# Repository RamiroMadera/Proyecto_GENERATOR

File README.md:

# GENERATOR 🎲  
**Consola electrónica portátil para jugar a la Generala**  
Dispositivo desarrollado con la **EDU-CIAA-NXP** que emula tiradas de dados, combinaciones y puntajes del tradicional juego de Generala. Integra una pantalla táctil, efectos de sonido, sensores de movimiento y una interfaz gráfica atractiva, todo en un sistema autónomo alimentado por batería.

---

## 🎮 Características principales

- **Simulación de tiradas de Generala**
  - Aleatorización de dados entre 1 y 6.
  - Selección de dados para conservar y volver a tirar.
  - Evaluación automática del puntaje y combinaciones.

- **Pantalla gráfica interactiva**
  - Display TFT 2.8" con controlador **ILI9341**.
  - Interfaz táctil basada en **XPT2046** para seleccionar dados y comenzar partidas.

- **Detección de movimiento**
  - Sensor **MPU6050** para identificar la agitación del dispositivo y gatillar la tirada.

- **Sistema de audio**
  - Generación de sonidos con DAC de 10 bits.
  - Amplificación mediante **LM386**.
  - Efectos que acompañan la agitación, la tirada y la obtención de una Generala.

- **Portabilidad total**
  - Alimentado por una batería externa de **5100 mAh**, con una autonomía estimada de más de **16 horas** de juego continuo.

---

## 🧠 Arquitectura del sistema

- **Microcontrolador:** EDU-CIAA-NXP  
- **Interacción por estados:** Inicio → Reposo → Sacudiendo 
- **Firmware en C** desarrollado bajo **CIAA Launcher** 

---

## 📦 Instalación

1. Clona el repositorio:
   ```bash
   git clone https://github.com/RamiroMadera/Proyecto_GENERATOR.git
   ```
2. Abrí el proyecto con CIAA Launcher.
3. Compila y carga el firmware a la placa.
4. Conecta los periféricos según el [esquemático incluido](https://github.com/RamiroMadera/Proyecto_GENERATOR/blob/main/kicad/GENERATOR_Esquematico.pdf).
5. ¡Listo para jugar!

---

## 📚 Documentación técnica

El proyecto cuenta con documentación completa en el informe final del curso "Taller de Proyecto I" de la Facultad de Ingeniería (UNLP), que incluye:

- Requerimientos de hardware y software
- Diseño esquemático y PCB en KiCad
- Arquitectura del firmware y máquina de estados
- Métodos de aleatorización
- Validación del sistema y videos de prueba

[📄 Informe Final (PDF)](https://github.com/RamiroMadera/Proyecto_GENERATOR/blob/main/docs/InformeFinal-Grupo8-TallerDeProyectoI.pdf)

---

## 🧪 Validación y videos

Se ha validado el correcto funcionamiento de todos los requerimientos. Puedes ver los resultados en esta [playlist de YouTube](https://www.youtube.com/playlist?list=PLVBSSKjP-CQ1Y1-SsgbkpVqvSBivJ-5Vr), que muestra:

- Encendido/apagado  
- Tiradas completas  
- Selección de dados  
- Sonido y efectos especiales  
- Reconocimiento de combinaciones y puntajes

---

## 🛠️ Créditos

**Autores:**  
- Tobias Garcia Iacovelli  
- Ramiro Madera  
- Ulises Pereira  

Este proyecto fue desarrollado como parte del curso **Taller de Proyecto I** en la **Facultad de Ingeniería, Universidad Nacional de La Plata**.

---

## 🚀 Próximos pasos

- Añadir sistema de historial de puntajes  
- Incorporar carcasa protectora  
- Expansión a múltiples juegos de dados  
- Conectividad en red para multijugador o leaderboard en la nube

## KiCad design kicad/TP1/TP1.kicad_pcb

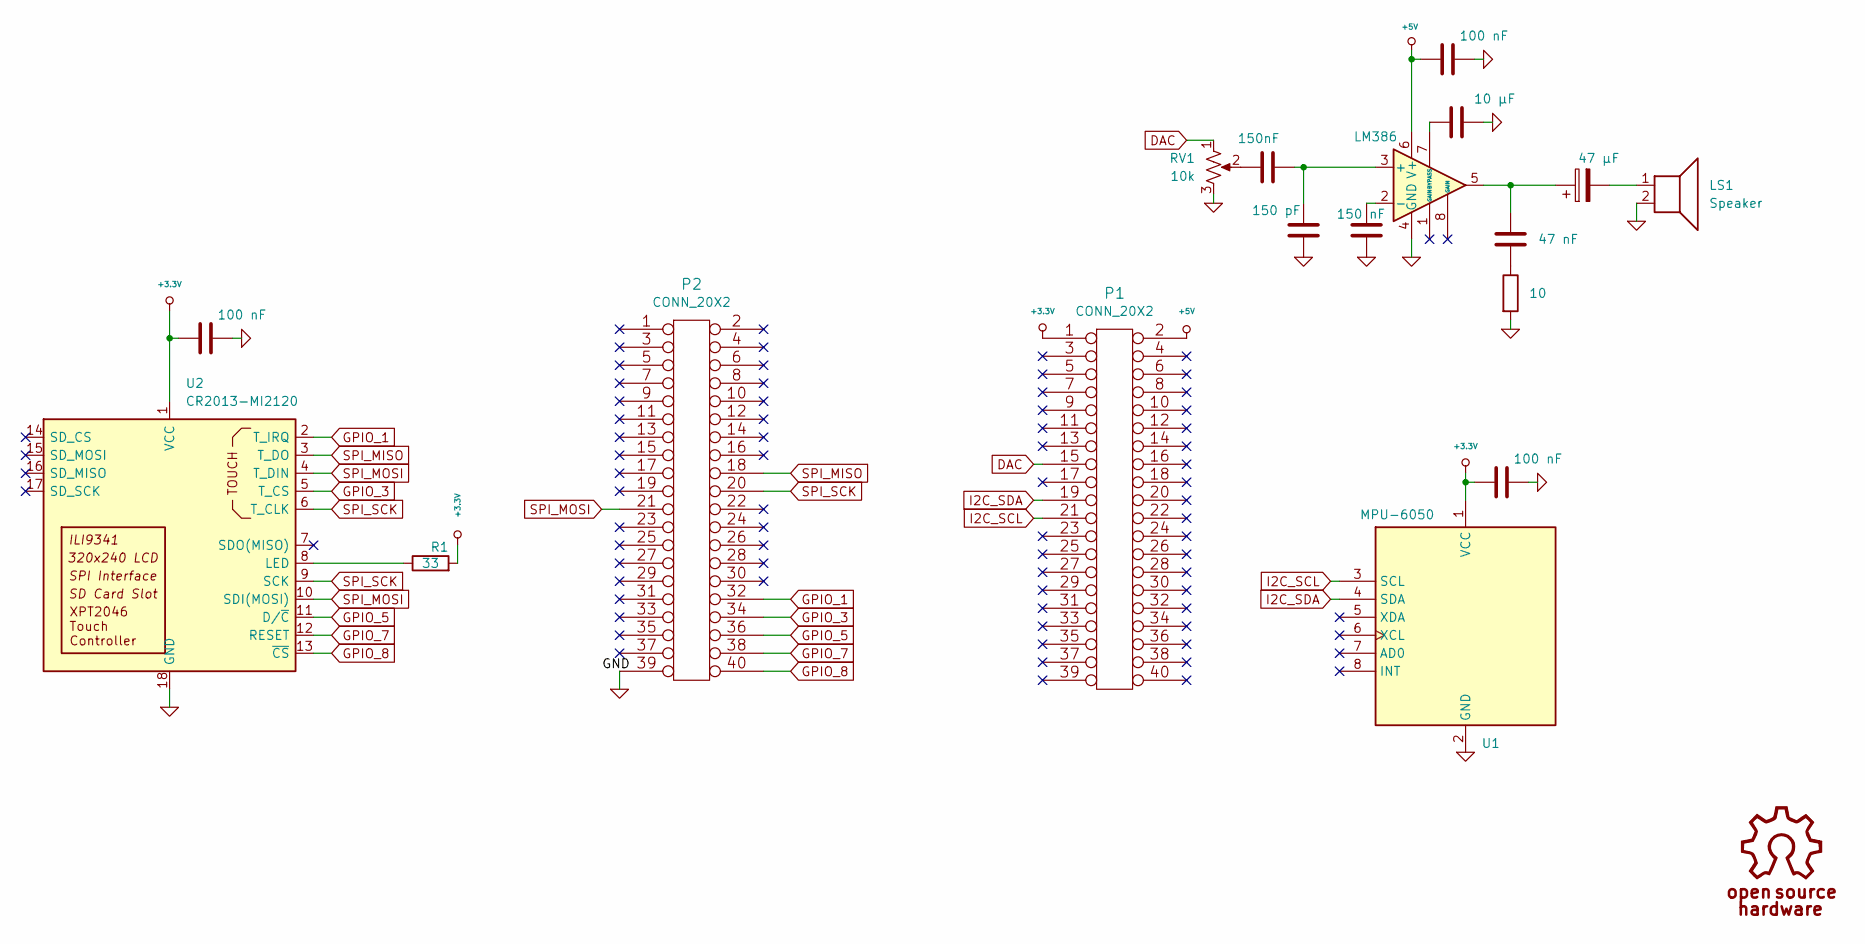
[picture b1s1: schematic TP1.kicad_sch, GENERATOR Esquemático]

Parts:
C1: 47 μF; CP_Radial_D8.0mm_P5.00mm
C2: 47 nF; C_Disc_D5.0mm_W2.5mm_P5.00mm
C3: 150nF; C_Disc_D5.0mm_W2.5mm_P5.00mm
C4: 150 pF; C_Disc_D5.0mm_W2.5mm_P5.00mm
C5: 150 nF; C_Disc_D5.0mm_W2.5mm_P5.00mm
C6, C8, C10: 100 nF; C_Disc_D5.0mm_W2.5mm_P5.00mm
C7: 10 μF; C_Disc_D5.0mm_W2.5mm_P5.00mm
LS1: Speaker; Buzzer_12x9.5RM7.6
P1, P2: CONN_20X2; PinSocket_2x20_P2.54mm_Vertical
R1: 33; R_Axial_DIN0207_L6.3mm_D2.5mm_P10.16mm_Horizontal
R2: 10; R_Axial_DIN0207_L6.3mm_D2.5mm_P10.16mm_Horizontal
RV1: 10k; Potentiometer_Piher_PT-6-V_Vertical
U1: MPU-6050; MPU-3050
U2: CR2013-MI2120; ILI_footprint
U4: LM386; DIP-8_W7.62mm

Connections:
+3.3V: C8.2, C10.2, P1.1, R1.2, U1.1 (VCC), U2.1 (VCC)
+5V: C6.2, P1.2, U4.6 (V+)
DAC: P1.15, RV1.1
GND: C4.1, C5.1, C6.1, C7.1, C8.1, C10.1, LS1.2, P2.39, R2.2, RV1.3, U1.2 (GND), U2.18 (GND), U4.4 (GND)
GPIO_1: P2.32, U2.2 (T_IRQ)
GPIO_3: P2.34, U2.5 (T_CS)
GPIO_5: P2.36, U2.11 (D/~C)
GPIO_7: P2.38, U2.12 (RESET)
GPIO_8: P2.40, U2.13 (~CS)
I2C_SCL: P1.21, U1.3 (SCL)
I2C_SDA: P1.19, U1.4 (SDA)
unnamed: C1.1, C2.2, U4.5
unnamed: C1.2, LS1.1
unnamed: C2.1, R2.1
unnamed: C3.1, RV1.2
unnamed: R1.1, U2.8 (LED)
unnamed: C3.2, C4.2, U4.3 (+)
unnamed: C5.2, U4.2 (-)
unnamed: C7.2, U4.7 (BYPASS)
SPI_MISO: P2.18, U2.3 (T_DO)
SPI_MOSI: P2.21, U2.4 (T_DIN), U2.10 (SDI(MOSI))
SPI_SCK: P2.20, U2.6 (T_CLK), U2.9 (SCK)

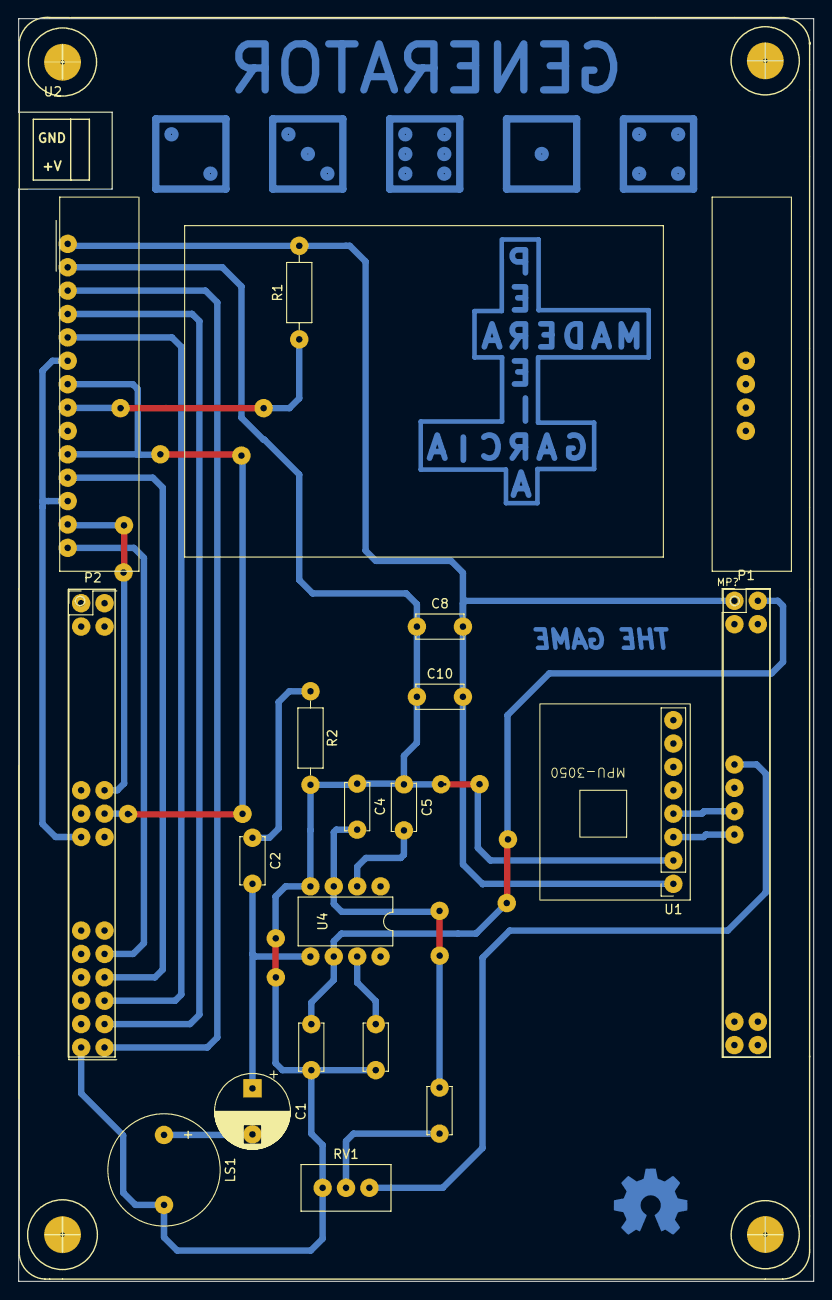
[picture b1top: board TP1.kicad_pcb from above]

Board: 2 copper layers, 86.4 x 137.2 mm, 21 parts (0 on the bottom side), 22 nets.

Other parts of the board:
G101, G101#2: Logo_OSHWA
MP?: Plantilla_EDU-CIAA

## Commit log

2024-10-10 commit inicial
2024-10-14 correcciones de la clase del 14/10
2024-10-15 Comentadas funciones set_region y fill_region, implementadas set_region_by_size y draw_pixel
2024-10-15 agregado un codigo de error para la funcion draw_pixel
2024-10-15 agregado codigo para probar libreria
2024-10-15 Agregadas dos librerías con herramientas gráficas a adaptar
2024-10-15 Modificacion en draw_pixel, implementacion de drawVLine y drawHLine
2024-10-15 Ya fue, portee directo el _writeLine
2024-10-26 correciones
2024-10-26 Subi la carpeta firmware_v3
2024-10-27 Aca esta lo que subio rama
2024-10-27 Avances en el driver del mpu
2024-10-28 Avances en clase: solucion de errores de la libreria
2024-10-30 Agrego primer borrador de librería
2024-10-31 agregado archivos de kicad
2024-10-31 fotos kicad
2024-11-01 Agrego bases para driver del touch
2024-11-01 Agregado "TP1" a carpeta kicad
2024-11-01 Agragados PDFs de kicad
2024-11-01 Actualizacion de Proyecto KiCad
2024-11-04 Cambio del programa de prueba, ahora usar la libreria MPU60X0 de sAPI
2024-11-05 Arreglos
2024-11-06 patch
2024-11-06 Ajuste de valores de configuración de hardware por default
2024-11-07 Actualizacion de KiCad
2024-11-11 Actualizacion Kicad
2024-11-11 patch kicad
2024-11-11 patch 2
2024-11-11 Agregadas pruebas de funciones de línea y píxel, trabajando en funciones para mostrar texto
2024-11-11 Agregadas funcionalidades de impresión de texto
2024-11-13 KiCad
2024-11-14 Incorporando spi en Touch
2024-11-14 Sacar acentto
2024-11-15 Correcciones de la clase
2024-11-19 Corrección Naranja
2024-11-20 Primera version de prueba del touch
2024-11-20 Primera prueba en terminal
2024-11-24 Listo para probar
2024-11-28 Archivos del Display
2024-11-28 patch nuevo poncho
2024-11-30 Correcciones para que ande
2024-12-05 Configurado de pines
2024-12-05 Cambios de configuracion de pines
2024-12-06 cambios varios
2024-12-06 Ahora la acceleracion se mide por magnitud, para que no importela inclinacion del dispositivo
2024-12-06 Ahora se toma en cuenta la medicion anterior para que la deteccion sea mas realista
2024-12-06 Reproducir onda sinusoidal
2024-12-06 Pruebas, no pude reproduir un sonido especifico todavia
2024-12-07 Pareceria estar funcionando, faltan pruebas
2024-12-07 Se agrego el sonido de victoria
2024-12-08 Correccion de errores
2024-12-08 Prueba impresión de imagen
2024-12-08 Prueba impresion de imagen con memoria dinamica
2024-12-09 Prueba pantalla
2024-12-09 Prueba sonido
2024-12-09 Librerias de pantalla
2024-12-10 Trabajo Martes 10 Diciembre
2024-12-10 Trabajo 10 Dic
2024-12-11 Primera Versión Full Funcional
2024-12-11 Emprolijamiento de estructuras de datos en táctil
2024-12-12 Borrador Interrupción
2024-12-12 Con codigo al final
2024-12-12 Código que hace UNA interrupción
2024-12-12 Interrupcion
2024-12-12 Esquemas dados
2024-12-13 Hechas funciones para dibujar la base de los dados, modificar los colores y dibujar los puntos
2024-12-13 Agregada funcion Randomizar_Dado()
2024-12-14 Prueba impresión de dados
2024-12-16 Codigo roto
2024-12-17 Prueba borde dados
2024-12-17 Parche
2024-12-17 Pruebas en la interrupción
2025-01-10 Modificacion de funciones para imprimir líneas horizontales y verticales + programa de prueba. Cambio menor en funciones para settear los colores de los dados
2025-01-11 Simplificación y reestructurado de función "ili9341_randomizar_dado" a "ili9341_dibujar_dado_numero"
2025-01-11 Parche (ajuste de dibujos de dados)
2025-01-14 Correcion de sintaxis
2025-01-20 intentos varios
2025-01-24 mas pruebas
2025-01-30 Prueba inicial (con alambres)
2025-01-31 cambio de parametros
2025-02-04 PROBAR: Simplificación de fución ili9341_spi_init(bitRate);
2025-02-04 Implementación de ili9341_paint_background();
2025-02-06 Correcciones
2025-02-06 Pasada en limpio
2025-02-07 Inicio del ultimo tiron
2025-02-07 int ili9341_seleccionarDado()
2025-02-08 Tactil Final
2025-02-08 Tactil Final en Carpeta Libs/Touch
2025-02-08 Se actualizo la libreria mpu6050
2025-02-09 Se creo la libreria sonidos
2025-02-09 Borron del menú de inicio
2025-02-09 Dibujoooo
2025-02-09 Deteccion de botones y dados en pantalla
2025-02-09 Primera pantalla de Inicio responsive
2025-02-10 Ajuste del boton de inicio
2025-02-10 Correcciones del CAD
2025-02-11 Seleccion de Dados y Calculo de Juegos y Puntajes
2025-02-11 Juegos agregados
2025-02-11 Ajustes varios
2025-02-11 Cambios en la libreria del mpu
2025-02-11 Se agregaron efectos de sonido
2025-02-12 Ajustes
2025-02-12 Correccion de multiples selecciones
2025-02-12 Randomizado hecho
2025-02-13 Randomizar numeros impresor mientras se sacude
2025-02-13 Parche en calculo de escalera
2025-02-17 Cambios estéticos
2025-02-17 Correcciones color de fondo de texto
2025-02-17 Parche colores
2025-04-12 Actualizacion read.md
